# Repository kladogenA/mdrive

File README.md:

# mdrive
A microdrive emulator for the Sinclair QL based on Raspberry Pico and an SD card reader.

This project aims to create a standalone microdive emulator for the Sinclair QL with an OLED screen, SD card reader and buttons used to selected the MDV image to make available to the QL.
It employs a Raspberry Pico that communicates with the QL through an 74LS125 line buffer for the Tracks and diodes for the rest of the pins.
This project is in a preliminary stage, partialy working.

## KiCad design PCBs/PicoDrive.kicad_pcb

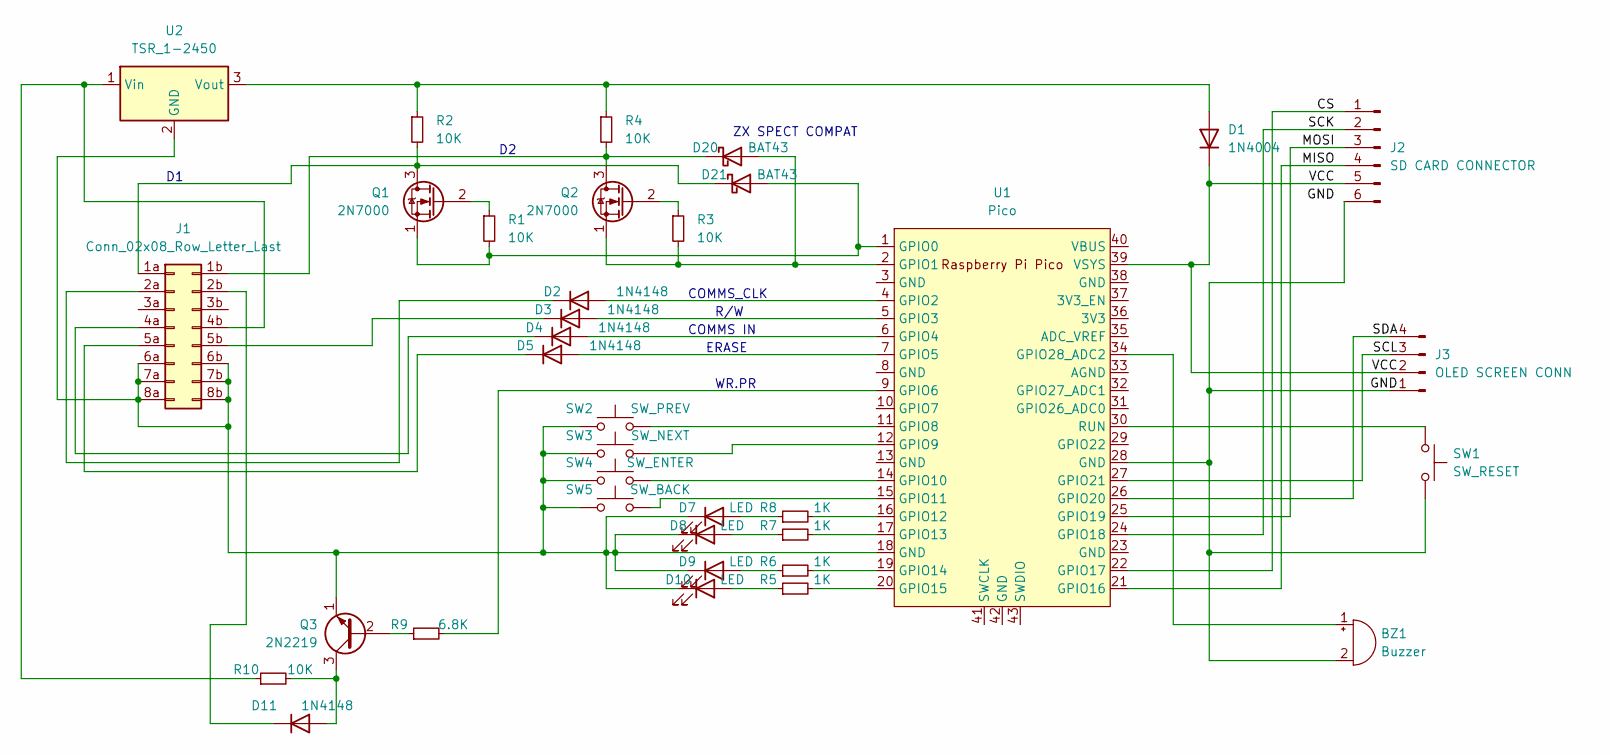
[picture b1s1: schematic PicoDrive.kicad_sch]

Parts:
BZ1: Buzzer; Buzzer_12x9.5RM7.6
D1: 1N4004; D_DO-41_SOD81_P10.16mm_Horizontal
D2, D3, D4, D5: 1N4148; D_DO-41_SOD81_P10.16mm_Horizontal
D7, D8, D9, D10: LED; LED_D3.0mm
D11: 1N4148; D_DO-35_SOD27_P7.62mm_Horizontal
D20, D21: BAT43; D_DO-35_SOD27_P7.62mm_Horizontal
J1: Conn_02x08_Row_Letter_Last; PinHeader_2x08_P2.54mm_Vertical_letters
J2: SD CARD CONNECTOR; PinHeader_1x06_P2.54mm_Vertical
J3: OLED SCREEN CONN; PinHeader_1x04_P2.54mm_Vertical
Q1, Q2: 2N7000; TO-92_Inline
Q3: 2N2219; TO-18-3
R1, R2, R3, R4, R10: 10K; R_Axial_DIN0204_L3.6mm_D1.6mm_P7.62mm_Horizontal
R5, R6, R7, R8: 1K; R_Axial_DIN0204_L3.6mm_D1.6mm_P7.62mm_Horizontal
R9: 6.8K; R_Axial_DIN0204_L3.6mm_D1.6mm_P7.62mm_Horizontal
SW1: SW_RESET; SW_PUSH_6mm
SW2: SW_PREV; SW_PUSH_6mm
SW3: SW_NEXT; SW_PUSH_6mm
SW4: SW_ENTER; SW_PUSH_6mm
SW5: SW_BACK; SW_PUSH_6mm
U1: Pico; RPi_Pico_SMD_TH
U2: TSR_1-2450; Converter_DCDC_TRACO_TSR-1_THT

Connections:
/CS: J2.1, U1.22 (GPIO17)
/MISO: J2.4, U1.21 (GPIO16)
/MOSI: J2.3, U1.25 (GPIO19)
/SCK: J2.2, U1.24 (GPIO18)
/VCC: D1.1 (K), J2.5, J3.2, U1.39 (VSYS)
unnamed: BZ1.1 (-), U1.34 (GPIO28_ADC2)
unnamed: D1.2 (A), R2.1, R4.1, U2.3 (Vout)
unnamed: D2.1 (K), J1.2a
unnamed: D2.2 (A), U1.4 (GPIO2)
unnamed: D3.1 (K), J1.5b
unnamed: D3.2 (A), U1.5 (GPIO3)
unnamed: D4.1 (K), J1.4a
unnamed: D4.2 (A), U1.6 (GPIO4)
unnamed: D5.1 (K), J1.5a
unnamed: D5.2 (A), U1.7 (GPIO5)
unnamed: D7.2 (A), R8.1
unnamed: D8.2 (A), R7.1
unnamed: D9.2 (A), R6.1
unnamed: D7.1 (K), D8.1 (K), D9.1 (K), D10.1 (K), J1.6a, J1.6b, J1.7a, J1.7b, J1.8a, J1.8b, Q3.1 (E), SW2.1, SW3.1, SW4.1, SW5.1, U1.18 (GND), U2.2 (GND)
unnamed: D10.2 (A), R5.1
unnamed: D11.1 (K), J1.2b
unnamed: D11.2 (A), Q3.3 (C), R10.2
unnamed: D20.1 (K), J1.1b, Q2.3 (D), R4.2
unnamed: D20.2 (A), Q2.1 (S), R3.2, U1.2 (GPIO1)
unnamed: D21.1 (K), J1.1a, Q1.3 (D), R2.2
unnamed: D21.2 (A), Q1.1 (S), R1.2, U1.1 (GPIO0)
unnamed: J1.4b, R10.1, U2.1 (Vin)
unnamed: BZ1.2 (+), J2.6, J3.1, SW1.2, U1.28 (GND)
unnamed: J3.3, U1.27 (GPIO21)
unnamed: J3.4, U1.26 (GPIO20)
unnamed: Q1.2 (G), R1.1
unnamed: Q2.2 (G), R3.1
unnamed: Q3.2 (B), R9.1
unnamed: R5.2, U1.20 (GPIO15)
unnamed: R6.2, U1.19 (GPIO14)
unnamed: R7.2, U1.17 (GPIO13)
unnamed: R8.2, U1.16 (GPIO12)
unnamed: R9.2, U1.9 (GPIO6)
unnamed: SW1.1, U1.30 (RUN)
unnamed: SW2.2, U1.11 (GPIO8)
unnamed: SW3.2, U1.12 (GPIO9)
unnamed: SW4.2, U1.14 (GPIO10)
unnamed: SW5.2, U1.15 (GPIO11)

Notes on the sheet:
R/W
ERASE
ZX SPECT COMPAT
COMMS_CLK
COMMS IN
WR.PR

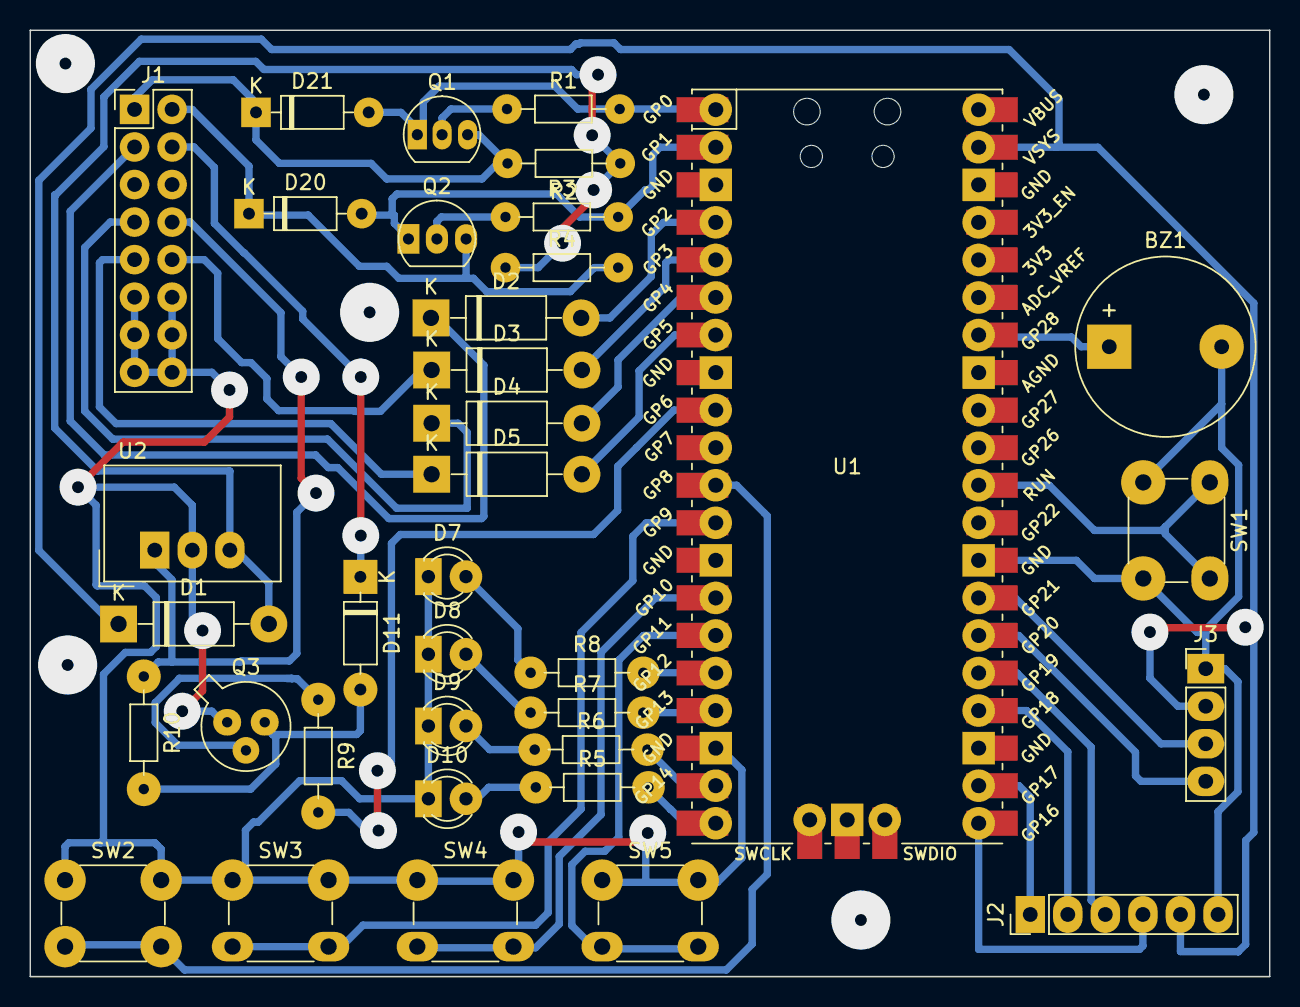
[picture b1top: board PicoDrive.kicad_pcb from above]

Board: 2 copper layers, 83.8 x 64.0 mm, 36 parts (0 on the bottom side), 43 nets.

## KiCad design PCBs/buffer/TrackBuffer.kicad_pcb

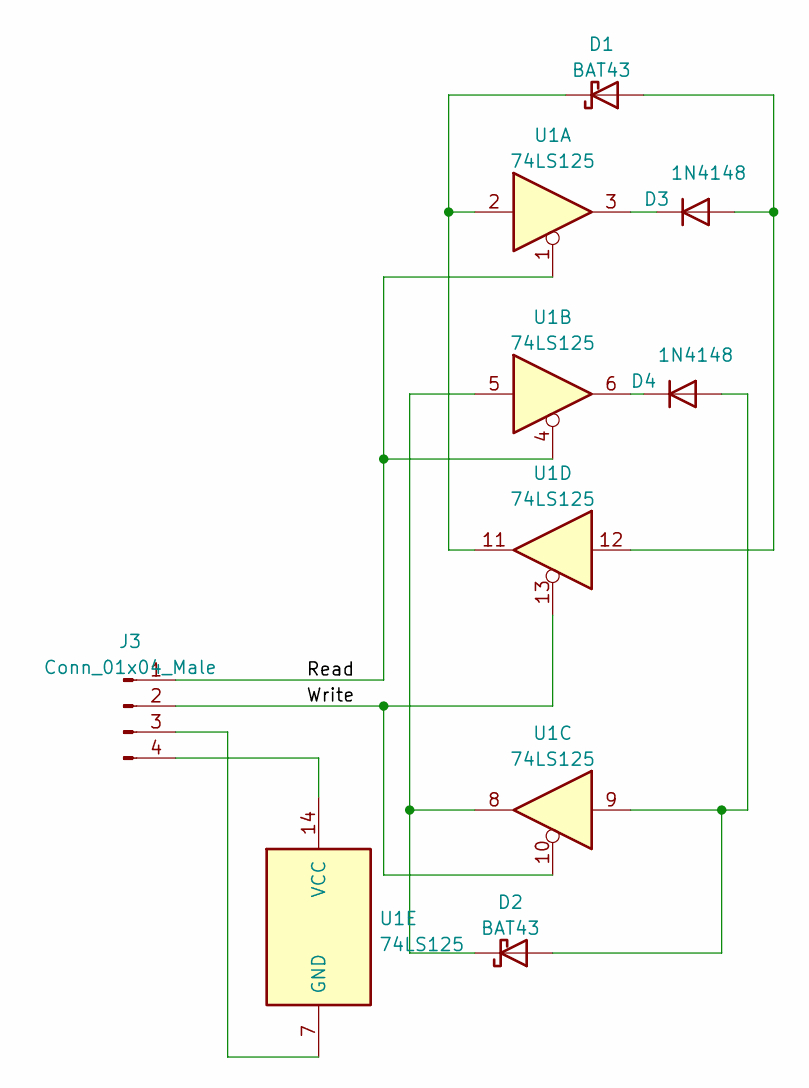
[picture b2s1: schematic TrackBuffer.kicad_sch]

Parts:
D1, D2: BAT43; D_DO-35_SOD27_P7.62mm_Horizontal
D3, D4: 1N4148; D_T-1_P5.08mm_Horizontal
J3: Conn_01x04_Male; PinHeader_1x04_P2.54mm_Vertical
U1: 74LS125

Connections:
/Read: J3.1, U1.1, U1.4
/Write: J3.2, U1.10, U1.13
unnamed: D2.1 (K), U1.5, U1.8
unnamed: D2.2 (A), D4.2 (A), U1.9
unnamed: D1.2 (A), D3.2 (A), U1.12
unnamed: J3.3, U1.7 (GND)
unnamed: J3.4, U1.14 (VCC)
unnamed: D3.1 (K), U1.3
unnamed: D4.1 (K), U1.6
unnamed: D1.1 (K), U1.2, U1.11

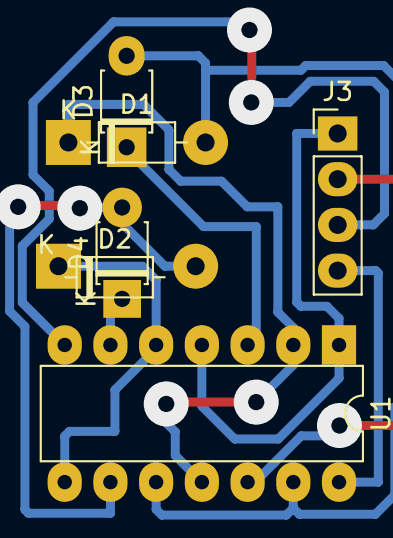
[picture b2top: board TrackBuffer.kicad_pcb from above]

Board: 2 copper layers, 6 parts (0 on the bottom side), 10 nets.

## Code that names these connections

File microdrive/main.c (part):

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typedef unsigned char byte;

/*
1A -> GPIO0 TRACK1
1B -> GPIO1 TRACK2 
2A -> GPIO2 COMMS_CLK
2B -> GPIO6 WR.PR
3A -> NC
3B -> NC
4A -> GPIO4 COMMS_IN
4B -> U2 9V
5A -> GPIO5 ERASE
5B -> GPIO3 R/W ON TEST QL Read High is 2.2V so connected directly without voltage divider
6A -> GND
6B -> GND
7A -> GND
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const int PIN_TRISTATE_BUFFER_QL_WRITE = 27;  //  ACTIVE LOW - Use this pin to send data from the QL to the PICO - YELLOW WIRE
const uint32_t MASK_TRISTATE_BUFFER_QL_WRITE = 1 << PIN_TRISTATE_BUFFER_QL_WRITE;

const int PIN_COMMS_IN    = 4;  // 4A -> GPIO4 COMMS_IN
const int PIN_WR_PROTECT  = 6;  // 2B -> GPIO6 WR.PR 
const int PIN_COMMS_CLK   = 2;  // 2A -> GPIO2 COMMS_CLK HIGH INACTIVE on IF1, LOW on QL; interrupt 
const int PIN_ERASE       = 5;  // 5A -> GPIO5 ERASE LOW active 
const int PIN_READ_WRITE  = 3;  // 5B -> GPIO3 R/W READ is HIGH; interrupt
const int PIN_TRACK_1     = 0;  // MDV_1A 
const int PIN_TRACK_2     = 1;  // MDV_1B

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
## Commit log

2023-06-16 Update main.c
    Removed timing check code.
2023-06-17 Description of the MDV sector data format
